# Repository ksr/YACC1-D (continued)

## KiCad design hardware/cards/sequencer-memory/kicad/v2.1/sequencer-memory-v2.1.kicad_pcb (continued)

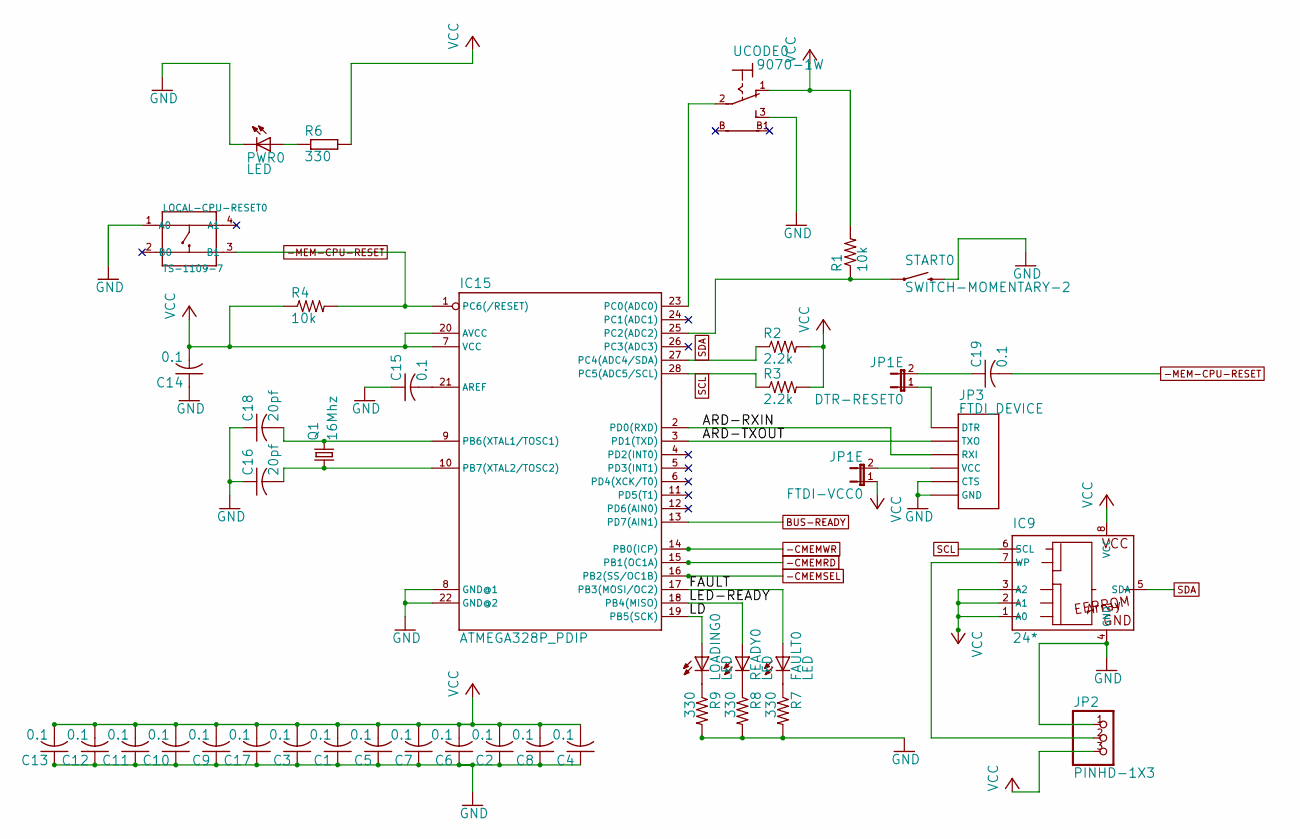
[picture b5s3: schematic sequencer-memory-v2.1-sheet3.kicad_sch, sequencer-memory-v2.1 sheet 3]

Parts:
C1, C2, C3, C4, C5, C6, C7, C8, C9, C10, C11, C12, C13, C14, C15, C17, C19: 0.1; C025-024X044
C16, C18: 20pf; C025-024X044
DTR-RESET0: JP1E; JP1
FAULT0: LED; LED5MM
FTDI-VCC0: JP1E; JP1
IC9: 24*; DIL8
IC15: ATMEGA328P_PDIP; DIL28-3
JP2: PINHD-1X3; 1X03
JP3: FTDI_DEVICE; FTDI_DEVICE_SIDE
LOADING0: LED; LED5MM
LOCAL-CPU-RESET0: TS-1109-7; SW4-6.2X6.2X5.0MM
PWR0: LED; LED5MM
Q1: 16Mhz; HC49_S
R1, R4: 10k; 0207_10
R2, R3: 2.2k; 0207_10
R6, R7, R8, R9: 330; 0207_10
READY0: LED; LED5MM
START0: SWITCH-MOMENTARY-2; TACTILE-PTH-SIDEEZ
UCODE0: 9070-1W

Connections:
-CMEMRD: IC15.15 (PB1(OC1A)); also elsewhere on the board
-CMEMSEL: IC15.16 (PB2(SS/OC1B)); also elsewhere on the board
-CMEMWR: IC15.14 (PB0(ICP)); also elsewhere on the board
-MEM-CPU-RESET: C19.2, IC15.1 (PC6(/RESET)), LOCAL-CPU-RESET0.3 (B1), R4.2; also elsewhere on the board
ARD-RXIN: IC15.2 (PD0(RXD)), JP3.P$3 (RXI)
ARD-TXOUT: IC15.3 (PD1(TXD)), JP3.P$2 (TXO)
BUS-READY: IC15.13 (PD7(AIN1)); also elsewhere on the board
FAULT: FAULT0.A, IC15.17 (PB3(MOSI/OC2))
GND: C1.1, C2.1, C3.1, C4.1, C5.1, C6.1, C7.1, C8.1, C9.1, C10.1, C11.1, C12.1, C13.1, C14.1, C15.1, C16.1, C17.1, C18.1, IC9.4 (GND), IC15.8 (GND@1), IC15.22 (GND@2), JP2.1, JP3.P$5 (CTS), JP3.P$6 (GND), LOCAL-CPU-RESET0.1 (A0), PWR0.K (C), R7.2, R8.2, R9.2, START0.2, UCODE0.3 (S); also elsewhere on the board
LD: IC15.19 (PB5(SCK)), LOADING0.A
LED-READY: IC15.18 (PB4(MISO)), READY0.A
unnamed: PWR0.A, R6.1
unnamed: C18.2, IC15.9 (PB6(XTAL1/TOSC1)), Q1.2
unnamed: C16.2, IC15.10 (PB7(XTAL2/TOSC2)), Q1.1
unnamed: C19.1, DTR-RESET0.2
unnamed: C15.2, IC15.21 (AREF)
unnamed: R8.1, READY0.K (C)
unnamed: LOADING0.K (C), R9.1
unnamed: FAULT0.K (C), R7.1
unnamed: IC15.23 (PC0(ADC0)), UCODE0.2
unnamed: IC9.7 (WP), JP2.2
unnamed: DTR-RESET0.1, JP3.P$1 (DTR)
unnamed: FTDI-VCC0.2, JP3.P$4 (VCC)
unnamed: IC15.25 (PC2(ADC2)), R1.1, START0.1
SCL: IC9.6 (SCL), IC15.28 (PC5(ADC5/SCL)), R3.1; also elsewhere on the board
SDA: IC9.5 (SDA), IC15.27 (PC4(ADC4/SDA)), R2.1; also elsewhere on the board
VCC: C1.2, C2.2, C3.2, C4.2, C5.2, C6.2, C7.2, C8.2, C9.2, C10.2, C11.2, C12.2, C13.2, C14.2, C17.2, FTDI-VCC0.1, IC9.1 (A0), IC9.2 (A1), IC9.3 (A2), IC9.8 (VCC), IC15.7 (VCC), IC15.20 (AVCC), JP2.3, R1.2, R2.2, R3.2, R4.1, R6.2, UCODE0.1 (O); also elsewhere on the board

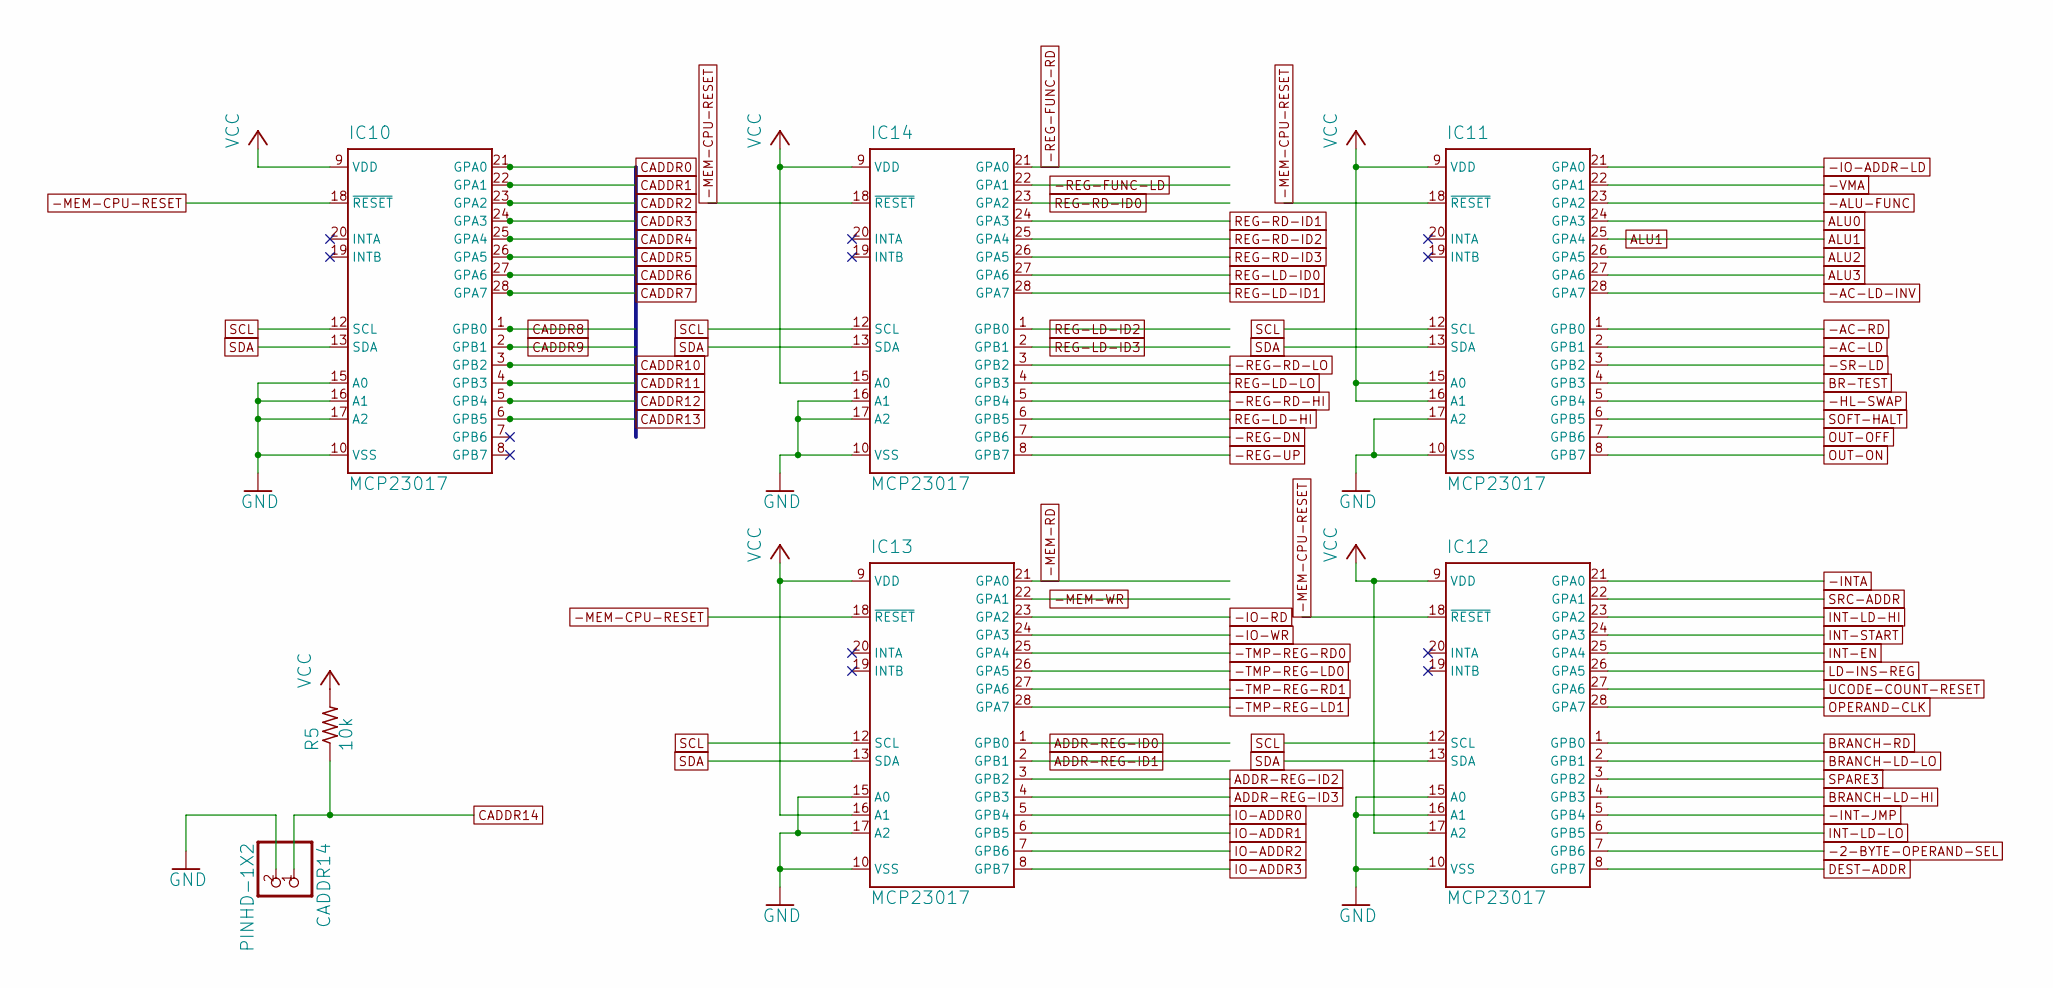
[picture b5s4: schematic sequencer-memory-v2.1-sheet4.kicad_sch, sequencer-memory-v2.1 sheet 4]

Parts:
CADDR14: PINHD-1X2; 1X02
IC10, IC11, IC12, IC13, IC14: MCP23017; DIL28-3
R5: 10k; 0207_10

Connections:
-2-BYTE-OPERAND-SEL: IC12.7 (GPB6); also elsewhere on the board
-AC-LD: IC11.2 (GPB1); also elsewhere on the board
-AC-LD-INV: IC11.28 (GPA7); also elsewhere on the board
-AC-RD: IC11.1 (GPB0); also elsewhere on the board
-ALU-FUNC: IC11.23 (GPA2); also elsewhere on the board
-HL-SWAP: IC11.5 (GPB4); also elsewhere on the board
-INT-JMP: IC12.5 (GPB4); also elsewhere on the board
-INTA: IC12.21 (GPA0); also elsewhere on the board
-IO-ADDR-LD: IC11.21 (GPA0); also elsewhere on the board
-IO-RD: IC13.23 (GPA2); also elsewhere on the board
-IO-WR: IC13.24 (GPA3); also elsewhere on the board
-MEM-CPU-RESET: IC10.18 (~RESET), IC11.18 (~RESET), IC12.18 (~RESET), IC13.18 (~RESET), IC14.18 (~RESET); also elsewhere on the board
-MEM-RD: IC13.21 (GPA0); also elsewhere on the board
-MEM-WR: IC13.22 (GPA1); also elsewhere on the board
-REG-DN: IC14.7 (GPB6); also elsewhere on the board
-REG-FUNC-LD: IC14.22 (GPA1); also elsewhere on the board
-REG-FUNC-RD: IC14.21 (GPA0); also elsewhere on the board
-REG-RD-HI: IC14.5 (GPB4); also elsewhere on the board
-REG-RD-LO: IC14.3 (GPB2); also elsewhere on the board
-REG-UP: IC14.8 (GPB7); also elsewhere on the board
-SR-LD: IC11.3 (GPB2); also elsewhere on the board
-TMP-REG-LD0: IC13.26 (GPA5); also elsewhere on the board
-TMP-REG-LD1: IC13.28 (GPA7); also elsewhere on the board
-TMP-REG-RD0: IC13.25 (GPA4); also elsewhere on the board
-TMP-REG-RD1: IC13.27 (GPA6); also elsewhere on the board
-VMA: IC11.22 (GPA1); also elsewhere on the board
ADDR-REG-ID0: IC13.1 (GPB0); also elsewhere on the board
ADDR-REG-ID1: IC13.2 (GPB1); also elsewhere on the board
ADDR-REG-ID2: IC13.3 (GPB2); also elsewhere on the board
ADDR-REG-ID3: IC13.4 (GPB3); also elsewhere on the board
ALU0: IC11.24 (GPA3); also elsewhere on the board
ALU1: IC11.25 (GPA4); also elsewhere on the board
ALU2: IC11.26 (GPA5); also elsewhere on the board
ALU3: IC11.27 (GPA6); also elsewhere on the board
BR-TEST: IC11.4 (GPB3); also elsewhere on the board
BRANCH-LD-HI: IC12.4 (GPB3); also elsewhere on the board
BRANCH-LD-LO: IC12.2 (GPB1); also elsewhere on the board
BRANCH-RD: IC12.1 (GPB0); also elsewhere on the board
CADDR0: IC10.21 (GPA0); also elsewhere on the board
CADDR1: IC10.22 (GPA1); also elsewhere on the board
CADDR2: IC10.23 (GPA2); also elsewhere on the board
CADDR3: IC10.24 (GPA3); also elsewhere on the board
CADDR4: IC10.25 (GPA4); also elsewhere on the board
CADDR5: IC10.26 (GPA5); also elsewhere on the board
CADDR6: IC10.27 (GPA6); also elsewhere on the board
CADDR7: IC10.28 (GPA7); also elsewhere on the board
CADDR8: IC10.1 (GPB0); also elsewhere on the board
CADDR9: IC10.2 (GPB1); also elsewhere on the board
CADDR10: IC10.3 (GPB2); also elsewhere on the board
CADDR11: IC10.4 (GPB3); also elsewhere on the board
CADDR12: IC10.5 (GPB4); also elsewhere on the board
CADDR13: IC10.6 (GPB5); also elsewhere on the board
CADDR14: CADDR14.1, R5.1; also elsewhere on the board
DEST-ADDR: IC12.8 (GPB7); also elsewhere on the board
GND: CADDR14.2, IC10.10 (VSS), IC10.15 (A0), IC10.16 (A1), IC10.17 (A2), IC11.10 (VSS), IC11.17 (A2), IC12.10 (VSS), IC12.15 (A0), IC12.16 (A1), IC13.10 (VSS), IC13.15 (A0), IC13.17 (A2), IC14.10 (VSS), IC14.16 (A1), IC14.17 (A2); also elsewhere on the board
INT-EN: IC12.25 (GPA4); also elsewhere on the board
INT-LD-HI: IC12.23 (GPA2); also elsewhere on the board
INT-LD-LO: IC12.6 (GPB5); also elsewhere on the board
INT-START: IC12.24 (GPA3); also elsewhere on the board
IO-ADDR0: IC13.5 (GPB4); also elsewhere on the board
IO-ADDR1: IC13.6 (GPB5); also elsewhere on the board
IO-ADDR2: IC13.7 (GPB6); also elsewhere on the board
IO-ADDR3: IC13.8 (GPB7); also elsewhere on the board
LD-INS-REG: IC12.26 (GPA5); also elsewhere on the board
OPERAND-CLK: IC12.28 (GPA7); also elsewhere on the board
OUT-OFF: IC11.7 (GPB6); also elsewhere on the board
OUT-ON: IC11.8 (GPB7); also elsewhere on the board
REG-LD-HI: IC14.6 (GPB5); also elsewhere on the board
REG-LD-ID0: IC14.27 (GPA6); also elsewhere on the board
REG-LD-ID1: IC14.28 (GPA7); also elsewhere on the board
REG-LD-ID2: IC14.1 (GPB0); also elsewhere on the board
REG-LD-ID3: IC14.2 (GPB1); also elsewhere on the board
REG-LD-LO: IC14.4 (GPB3); also elsewhere on the board
REG-RD-ID0: IC14.23 (GPA2); also elsewhere on the board
REG-RD-ID1: IC14.24 (GPA3); also elsewhere on the board
REG-RD-ID2: IC14.25 (GPA4); also elsewhere on the board
REG-RD-ID3: IC14.26 (GPA5); also elsewhere on the board
SCL: IC10.12 (SCL), IC11.12 (SCL), IC12.12 (SCL), IC13.12 (SCL), IC14.12 (SCL); also elsewhere on the board
SDA: IC10.13 (SDA), IC11.13 (SDA), IC12.13 (SDA), IC13.13 (SDA), IC14.13 (SDA); also elsewhere on the board
SOFT-HALT: IC11.6 (GPB5); also elsewhere on the board
SPARE3: IC12.3 (GPB2); also elsewhere on the board
SRC-ADDR: IC12.22 (GPA1); also elsewhere on the board
UCODE-COUNT-RESET: IC12.27 (GPA6); also elsewhere on the board
VCC: IC10.9 (VDD), IC11.9 (VDD), IC11.15 (A0), IC11.16 (A1), IC12.9 (VDD), IC12.17 (A2), IC13.9 (VDD), IC13.16 (A1), IC14.9 (VDD), IC14.15 (A0), R5.2; also elsewhere on the board

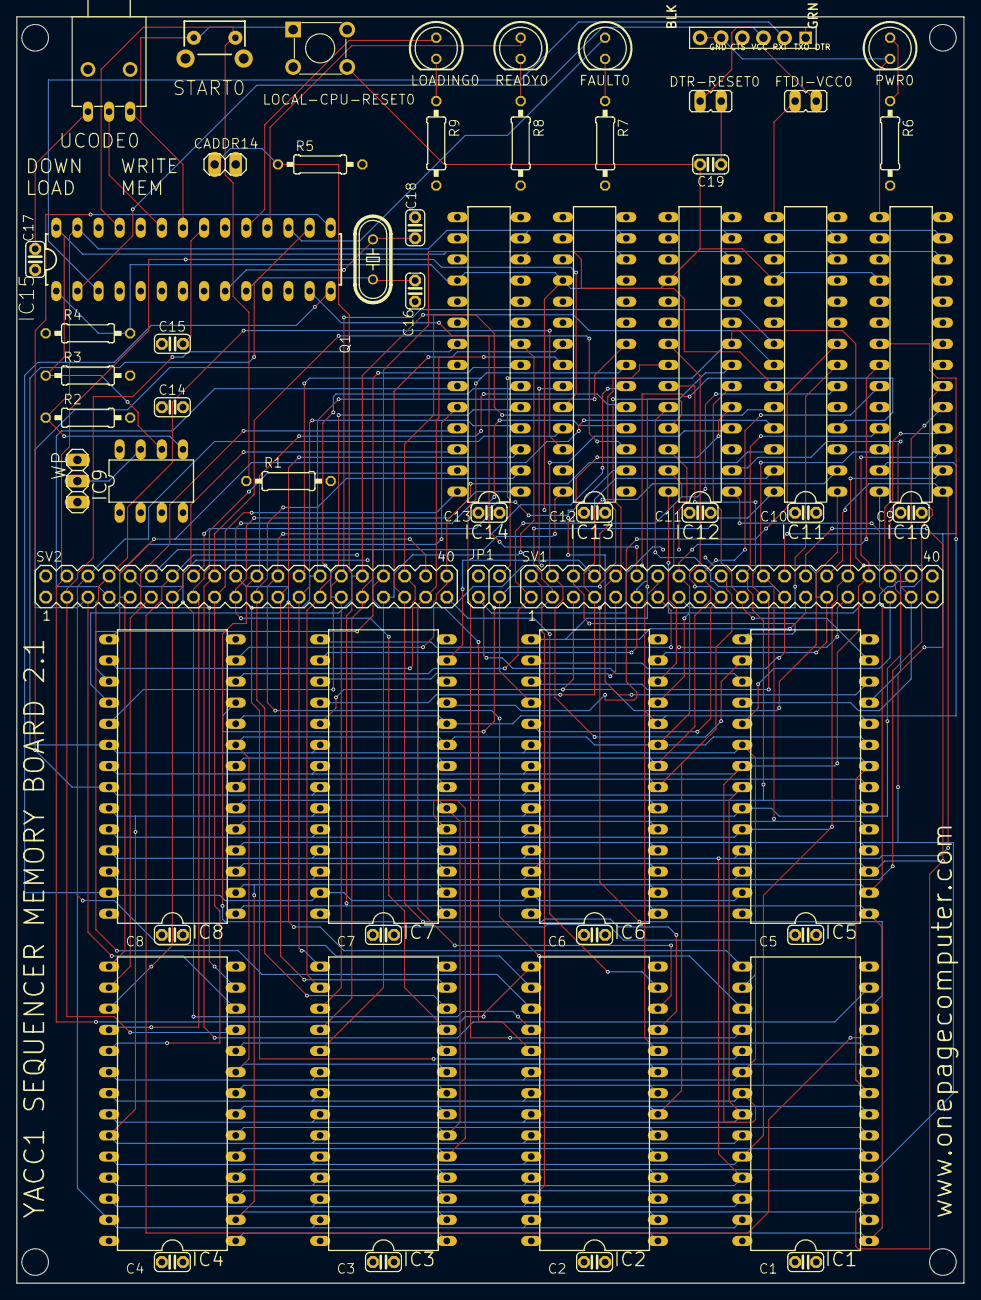
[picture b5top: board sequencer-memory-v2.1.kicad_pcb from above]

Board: 4 copper layers, 114.0 x 152.4 mm, 63 parts (0 on the bottom side), 106 nets.

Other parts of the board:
UNK_HOLE_0: dummyfp0
UNK_HOLE_1: dummyfp1
UNK_HOLE_2: dummyfp2
UNK_HOLE_3: dummyfp3

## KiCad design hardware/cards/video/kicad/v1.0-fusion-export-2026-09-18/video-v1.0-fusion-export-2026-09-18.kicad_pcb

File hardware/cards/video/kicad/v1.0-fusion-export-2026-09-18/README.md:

# video-v1.0-fusion-export-2026-09-18 — KiCad conversion

Generated 2026-09-23 by `tools/eagle_to_kicad_all.py` from the Eagle design `Video_1.0` in `hardware/cards/video/eagle/v1.0-fusion-export-2026-09-18/`. **The Eagle files are the record of what was designed and built; this KiCad project is derived from them and is regenerated from scratch on every run of the tool** (hand edits here will be lost - once a card is edited in KiCad, remove it from the tool's list). This revision was FABRICATED (see `hardware/FABRICATED.md`).

## Files

| File | What it is |
|---|---|
| `video-v1.0-fusion-export-2026-09-18.kicad_pro` | project; OSH Park rules (6 mil track, 5 mil clearance, 10 mil drill, 4 mil annular) |
| `video-v1.0-fusion-export-2026-09-18.kicad_sch` | root sheet; 2 sub-sheet(s) `video-v1.0-fusion-export-2026-09-18-sheetN.kicad_sch` mirror the Eagle sheets |
| `video-v1.0-fusion-export-2026-09-18-eagle.kicad_sym` | project symbol library generated from the Eagle libraries used (units = Eagle gates) |
| `video-v1.0-fusion-export-2026-09-18.kicad_pcb` | the board: 2 copper layers, 47 footprints, 1180 track segments, 96 vias |
| `video-v1.0-fusion-export-2026-09-18-eagle.pretty/` | project footprint library extracted from the imported board |
| `reports/` | ERC (`erc.json`), DRC (`drc.json`), schematic PDF, board renders (`-top.png`, `-bottom.png`), netlist + `netlist-compare.txt` |

## Proof

Schematic-vs-board netlist comparison (`tools/kicad/compare_netlists.py`: every (reference, pad) partition must be identical): **MISMATCH (115/117 nets)**

```
  ONLY IN SCHEMATIC +5V        [('C16', '+'), ('C17', '1'), ('C18', '1'), ('C19', '1'), ('C20', '1'), ('C21', '1'), ('C22', '1'), ('C23', '1'), ('C24', '1'), ('C25', '1'), ('C26', '1'), ('C27', '1'), ('C28', '1'), ('C29', '1'), ('C3', '1'), ('IC15', '2'), ('R10', '2'), ('R12', '1'), ('RN2', '1')]
  ONLY IN SCHEMATIC VCC        [('IC1', '14'), ('IC15', '48'), ('IC17', '20'), ('IC18', '16'), ('IC19', '14'), ('IC2', '20'), ('IC20', '14'), ('IC21', '5'), ('IC22', '16'), ('IC23', '16'), ('IC24', '16'), ('IC25', '24'), ('IC26', '14'), ('IC27', '14'), ('IC28', '16'), ('JP1', '3'), ('R2', '2'), ('X1', 'A2'), ('X1', 'A31'), ('X1', 'B2'), ('X1', 'B31'), ('X1', 'C2'), ('X1', 'C31')]
  ONLY ON BOARD     +5V        [('C16', '+'), ('C17', '1'), ('C18', '1'), ('C19', '1'), ('C20', '1'), ('C21', '1'), ('C22', '1'), ('C23', '1'), ('C24', '1'), ('C25', '1'), ('C26', '1'), ('C27', '1'), ('C28', '1'), ('C29', '1'), ('C3', '1'), ('IC1', '14'), ('IC15', '2'), ('IC2', '20'), ('R10', '2'), ('R12', '1'), ('RN2', '1')]
  ONLY ON BOARD     VCC        [('IC15', '48'), ('IC17', '20'), ('IC18', '16'), ('IC19', '14'), ('IC20', '14'), ('IC21', '5'), ('IC22', '16'), ('IC23', '16'), ('IC24', '16'), ('IC25', '24'), ('IC26', '14'), ('IC27', '14'), ('IC28', '16'), ('JP1', '3'), ('R2', '2'), ('X1', 'A2'), ('X1', 'A31'), ('X1', 'B2'), ('X1', 'B31'), ('X1', 'C2'), ('X1', 'C31')]
  same connectivity, different net name: [('/Sheet 1/BOARDSEL', 'BOARDSEL'), ('/Sheet 1/CHARCLOCK', 'CHARCLOCK'), ('/Sheet 1/CLK', 'CLK'), ('/Sheet 1/CRTCCLOCK', 'CRTCCLOCK'), ('/Sheet 1/DOTCLOCK', 'DOTCLOCK'), ('/Sheet 1/VADDR0', 'VADDR0'), ('/Sheet 1/VADDR1', 'VADDR1'), ('/Sheet 1/VADDR2', 'VADDR2'), ('/Sheet 1/VADDR3', 'VADDR3'), ('/Sheet 1/VADDR4', 'VADDR4'), ('/Sheet 1/VADDR5', 'VADDR5'), ('/Sheet 1/VADDR6', 'VADDR6'), ('/Sheet 1/VADDR7', 'VADDR7'), ('/Sheet 1/VADDR8', 'VADDR8'), ('/Sheet 1/VADDR9', 'VADDR9'), ('/Sheet 1/VADDR10', 'VADDR10'), ('/Sheet 1/VADDR11', 'VADDR11'), ('/Sheet 1/VDATA0', 'VDATA0'), ('/Sheet 1/VDATA1', 'VDATA1'), ('/Sheet 1/VDATA2', 'VDATA2'), ('/Sheet 1/VDATA3', 'VDATA3'), ('/Sheet 1/VDATA4', 'VDATA4'), ('/Sheet 1/VDATA5', 'VDATA5'), ('/Sheet 1/VDATA7', 'VDATA7'), ('/Sheet 1/VROWS0', 'VROWS0'), ('/Sheet 1/VROWS1', 'VROWS1'), ('/Sheet 1/VROWS2', 'VROWS2'), ('Net-(IC1A-I0)', 'N$1'), ('Net-(IC1A-I1)', 'N$4'), ('Net-(IC1B-O)', 'N$17'), ('Net-(IC1C-O)', 'N$6'), ('Net-(IC1D-I1)', 'N$5'), ('Net-(IC2-1D)', 'N$15'), ('Net-(IC2-2D)', 'N$14'), ('Net-(IC2-3D)', 'N$13'), ('Net-(IC2-4D)', 'N$12'), ('Net-(IC2-5D)', 'N$10'), ('Net-(IC2-6D)', 'N$9'), ('Net-(IC2-7D)', 'N$8'), ('Net-(IC2-8D)', 'N$7'), ('Net-(IC2-ENC)', 'N$18'), ('Net-(IC2-OC)', 'N$16'), ('Net-(IC15-~{CER})', 'N$52'), ('Net-(IC17-CS)', 'N$91'), ('Net-(IC17-CURSOR)', 'N$74'), ('Net-(IC17-DE)', 'N$79'), ('Net-(IC17-HS)', 'N$83'), ('Net-(IC17-VS)', 'N$82'), ('Net-(IC18-A0)', 'N$48'), ('Net-(IC18-A1)', 'N$49'), ('Net-(IC18-A2)', 'N$50'), ('Net-(IC18-A3)', 'N$51'), ('Net-(IC18-A=B_I)', 'N$89'), ('Net-(IC19A-I1)', 'N$2'), ('Net-(IC19B-I1)', 'N$87'), ('Net-(IC19C-I0)', 'N$60'), ('Net-(IC19D-I0)', 'N$80'), ('Net-(IC19D-I1)', 'N$81'), ('Net-(IC19D-O)', 'N$84'), ('Net-(IC20A-I)', 'N$54'), ('Net-(IC20A-O)', 'N$56'), ('Net-(IC20B-O)', 'N$55'), ('Net-(IC20C-O)', 'N$57'), ('Net-(IC20D-I)', 'N$58'), ('Net-(IC20D-O)', 'N$59'), ('Net-(IC22-CLR)', 'N$73'), ('Net-(IC22-D1)', 'N$75'), ('Net-(IC22-D2)', 'N$61'), ('Net-(IC22-D4)', 'N$78'), ('Net-(IC22-Q2)', 'N$76'), ('Net-(IC23-Q1)', 'N$67'), ('Net-(IC23-Q2)', 'N$68'), ('Net-(IC23-Q3)', 'N$69'), ('Net-(IC23-Q4)', 'N$70'), ('Net-(IC23-Q5)', 'N$71'), ('Net-(IC23-Q6)', 'N$72'), ('Net-(IC24-D)', 'N$62'), ('Net-(IC24-E)', 'N$63'), ('Net-(IC24-F)', 'N$64'), ('Net-(IC24-G)', 'N$65'), ('Net-(IC24-H)', 'N$66'), ('Net-(IC24-QH)', 'N$77'), ('Net-(IC27A-O)', 'N$86'), ('Net-(IC27B-O)', 'N$85'), ('Net-(IC27F-O)', 'N$3'), ('Net-(PWR0-PadA)', 'N$11')]
```

## Readability

`tools/kicad/sch_overlaps.py` over every sheet: text over text 0, text over a symbol body 19, text crossed by a line 6, items off the drawing frame or on the title block 0. What is left is mostly the Eagle drawing itself (parts placed that close in Eagle) or KiCad drawing pin numbers centred on short pins.

## Residual ERC / DRC

ERC by type: endpoint_off_grid 35, isolated_pin_label 56, pin_not_driven 2, pin_to_pin 8, unconnected_wire_endpoint 21.
`isolated_pin_label` = the converter's per-net global labels (cosmetic); `power_pin_not_driven` / unused-unit notes are the same ones KiCad's own Eagle importer leaves. `unconnected_wire_endpoint` / `pin_not_connected` = wire stubs Eagle leaves bare (mostly net wires ending on a bus, which is drawn as graphics here); since 2026-09-23 the converter no longer hangs a label on every such end (that was most of the label clutter), so they show as KiCad warnings.

DRC by type: items_not_allowed 2, lib_footprint_mismatch 3, silk_edge_clearance 8, silk_over_copper 199, silk_overlap 15, text_height 2; unconnected items 0; schematic parity 0.
Silk-over-pad and clearance notes reflect the Eagle design as drawn; unconnected items are Eagle airwires (parts the design left unrouted).

Converter: converted: 192 symbols, 549 wires, 189 labels, 90 junctions, 10 bus lines, 30 no-connects

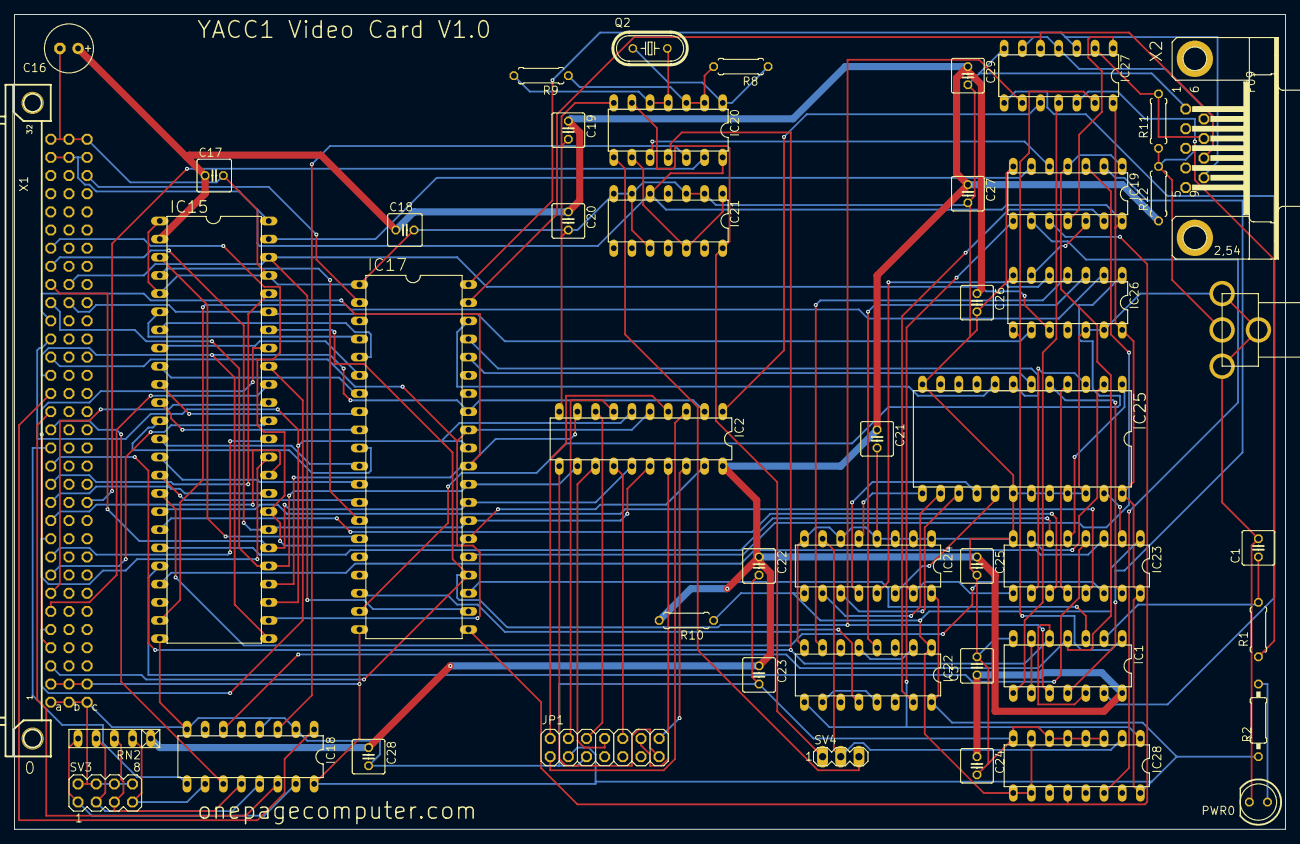
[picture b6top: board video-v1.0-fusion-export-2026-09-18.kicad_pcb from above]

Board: 2 copper layers, 177.8 x 114.0 mm, 47 parts (0 on the bottom side), 117 nets.

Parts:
C1: 1; C025-050X050
C3, C17, C18, C19, C20, C21, C22, C23, C24, C25, C26, C27, C28, C29: .1; C025-050X050
C16: 10.0; E2,5-7
IC1: 74ALS08N; DIL14
IC2: 74LS373N; DIL20
IC15: VRAM; DIL48
IC17: 6845; DIL40
IC18: 74S85N; DIL16
IC19: 74LS00N; DIL14
IC20: 74LS04N; DIL14
IC21: 74LS90N; DIL14
IC22: 74LS175N; DIL16
IC23: 74LS174N; DIL16
IC24: 74LS166N; DIL16
IC25: CHARGEN; DIL24
IC26: 74LS86N; DIL14
IC27: 7416N; DIL14
IC28: 74HC160N; DIL16
JP1: PINHD-2X7; 2X07
PWR0: LED5MM
Q2: HC49U-V
R1: 10K; 0207_7
R2: 330; 0207_10
R8, R9, R10: 1K; 0207_7
R11: 33; 0207_7
R12: 270; 0207_7
RN2: RN-5
SV3: MA04-2
SV4: MA03-1
U$3: RCA
X1: FABC96R
X2: F09HP

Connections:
+5V: C3.1, C16.+, C17.1, C18.1, C19.1, C20.1, C21.1, C22.1, C23.1, C24.1, C25.1, C26.1, C27.1, C28.1, C29.1, IC1.14, IC2.20, IC15.2, R10.2, R12.1, RN2.1
-MEM-RD: IC15.43, IC26.9, X1.B23
-MEM-WR: IC15.46, IC17.22, IC26.10, X1.B24
-RESET: IC17.2, X1.C30
-VMA: IC20.13, X1.C12
ADDR0: IC1.10, IC15.42, IC17.24, IC27.9, X1.A3
ADDR1: IC15.41, X1.A4
ADDR2: IC15.40, X1.A5
ADDR3: IC15.39, X1.A6
ADDR4: IC15.38, X1.A7
ADDR5: IC15.37, X1.A8
ADDR6: IC15.36, X1.A9
ADDR7: IC15.35, X1.A10
ADDR8: IC15.34, X1.A11
ADDR9: IC15.33, X1.A12
ADDR10: IC15.44, X1.A13
ADDR11: IC1.5, IC1.12, IC20.11, X1.A14
ADDR12: IC18.9, X1.A15
ADDR13: IC18.11, X1.A16
ADDR14: IC18.14, X1.A17
ADDR15: IC18.1, X1.A18
BOARDSEL: IC1.4, IC18.6, IC19.1, IC19.4
CHARCLOCK: IC19.8, IC22.9, IC23.9, IC24.15, IC28.1
CLK: IC1.3, IC17.23
CRTCCLOCK: IC17.21, IC19.10, IC28.12
DATA0: IC2.2, IC15.25, IC17.33, X1.A19
DATA1: IC2.5, IC15.26, IC17.32, X1.A20
DATA2: IC2.6, IC15.27, IC17.31, X1.A21
DATA3: IC2.9, IC15.28, IC17.30, X1.A22
DATA4: IC2.12, IC15.29, IC17.29, X1.A23
DATA5: IC2.15, IC15.30, IC17.28, X1.A24
DATA6: IC2.16, IC15.31, IC17.27, X1.A25
DATA7: IC2.19, IC15.32, IC17.26, X1.A26
DOTCLOCK: IC24.7, IC28.2, SV4.2
GND: C1.2, C3.2, C16.-, C17.2, C18.2, C19.2, C20.2, C21.2, C22.2, C23.2, C24.2, C25.2, C26.2, C27.2, C28.2, C29.2, IC1.7, IC2.10, IC15.1, IC15.5, IC15.24, IC15.45, IC17.1, IC18.2, IC18.4, IC18.8, IC19.7, IC20.7, IC21.2, IC21.3, IC21.6, IC21.7, IC21.10, IC22.8, IC23.8, IC24.1, IC24.2, IC24.3, IC24.4, IC24.6, IC24.8, IC25.12, IC25.18, IC25.19, IC25.20, IC25.21, IC25.22, IC26.7, IC26.12, IC26.13, IC27.7, IC28.3, IC28.4, IC28.5, IC28.6, IC28.8, JP1.5, PWR0.K, SV3.2, SV3.4, SV3.6, SV3.8, U$3.S1, U$3.S2, U$3.S3, X1.A1, X1.A32, X1.B1, X1.B32, X1.C1, X1.C32, X2.1
unnamed: IC1.1, IC26.8, IC27.13
unnamed: IC1.11, IC19.2
unnamed: IC27.12, R1.1
unnamed: C1.1, IC1.2, R1.2
unnamed: IC1.13, IC27.8
unnamed: IC1.8, IC27.11
unnamed: IC2.18, JP1.14
unnamed: IC2.17, JP1.12
unnamed: IC2.14, JP1.10
unnamed: IC2.13, JP1.8
unnamed: PWR0.A, R2.1
unnamed: IC2.8, JP1.6
unnamed: IC2.7, JP1.4
unnamed: IC2.4, JP1.2
unnamed: IC2.3, JP1.1
unnamed: IC2.1, IC27.10
unnamed: IC1.6, IC1.9
unnamed: IC2.11, JP1.13
unnamed: IC18.10, RN2.2, SV3.7
unnamed: IC18.12, RN2.3, SV3.5
unnamed: IC18.13, RN2.4, SV3.3
unnamed: IC18.15, RN2.5, SV3.1
unnamed: IC15.47, IC19.6
unnamed: IC20.1, Q2.1, R8.1
unnamed: IC20.4, IC20.5, Q2.2, R9.2
unnamed: IC20.2, IC20.3, R8.2, R9.1
unnamed: IC20.6, IC21.14, SV4.1
unnamed: IC20.9, IC21.1, IC21.12
unnamed: IC20.8, SV4.3
unnamed: IC19.9, IC28.14
unnamed: IC22.2, IC22.5
unnamed: IC24.5, IC25.13
unnamed: IC24.10, IC25.14
unnamed: IC24.11, IC25.15
unnamed: IC24.12, IC25.16
unnamed: IC24.14, IC25.17
unnamed: IC23.2, IC25.23
unnamed: IC23.5, IC25.1
unnamed: IC23.7, IC25.2
unnamed: IC23.10, IC25.3
unnamed: IC23.12, IC25.4
unnamed: IC23.15, IC25.5
unnamed: IC22.1, IC23.1, IC24.9, IC28.7, IC28.9, IC28.10, R10.1
unnamed: IC17.19, IC26.1
unnamed: IC22.4, IC26.3
unnamed: IC22.7, IC26.4
unnamed: IC24.13, IC26.5
unnamed: IC22.10, IC22.13
unnamed: IC17.18, IC22.12
unnamed: IC19.12, IC26.6
unnamed: IC19.13, IC22.15
unnamed: IC17.40, IC27.3, X2.9
unnamed: IC17.39, IC27.5, X2.8
unnamed: IC19.11, IC27.1
unnamed: IC27.4, IC27.6, R11.1, R12.2, U$3.C1
unnamed: IC27.2, R11.2, X2.7
unnamed: IC19.5, IC20.10
unnamed: IC18.3, IC20.12
unnamed: IC17.25, IC19.3
VADDR0: IC15.6, IC17.4
VADDR1: IC15.7, IC17.5
VADDR2: IC15.8, IC17.6
VADDR3: IC15.9, IC17.7
VADDR4: IC15.10, IC17.8
VADDR5: IC15.11, IC17.9
VADDR6: IC15.12, IC17.10
VADDR7: IC15.13, IC17.11
VADDR8: IC15.14, IC17.12
VADDR9: IC15.15, IC17.13
VADDR10: IC15.4, IC17.14
VADDR11: IC15.3, IC17.15
VCC: IC15.48, IC17.20, IC18.16, IC19.14, IC20.14, IC21.5, IC22.16, IC23.16, IC24.16, IC25.24, IC26.14, IC27.14, IC28.16, JP1.3, R2.2, X1.A2, X1.A31, X1.B2, X1.B31, X1.C2, X1.C31
VDATA0: IC15.16, IC23.14
VDATA1: IC15.17, IC23.13
VDATA2: IC15.18, IC23.11
VDATA3: IC15.19, IC23.6
VDATA4: IC15.20, IC23.4
VDATA5: IC15.21, IC23.3
VDATA7: IC15.23, IC26.2
VROWS0: IC17.38, IC25.8
VROWS1: IC17.37, IC25.7
VROWS2: IC17.36, IC25.6
